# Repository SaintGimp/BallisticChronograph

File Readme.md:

This project is heavily based on https://github.com/td0g/ballistic_chronograph_mk2 but modified to use phototransistors rather than photodiodes, mostly because components for the boost converter in the original design are really hard to source right now, and I also wanted to optimize for my own use cases.

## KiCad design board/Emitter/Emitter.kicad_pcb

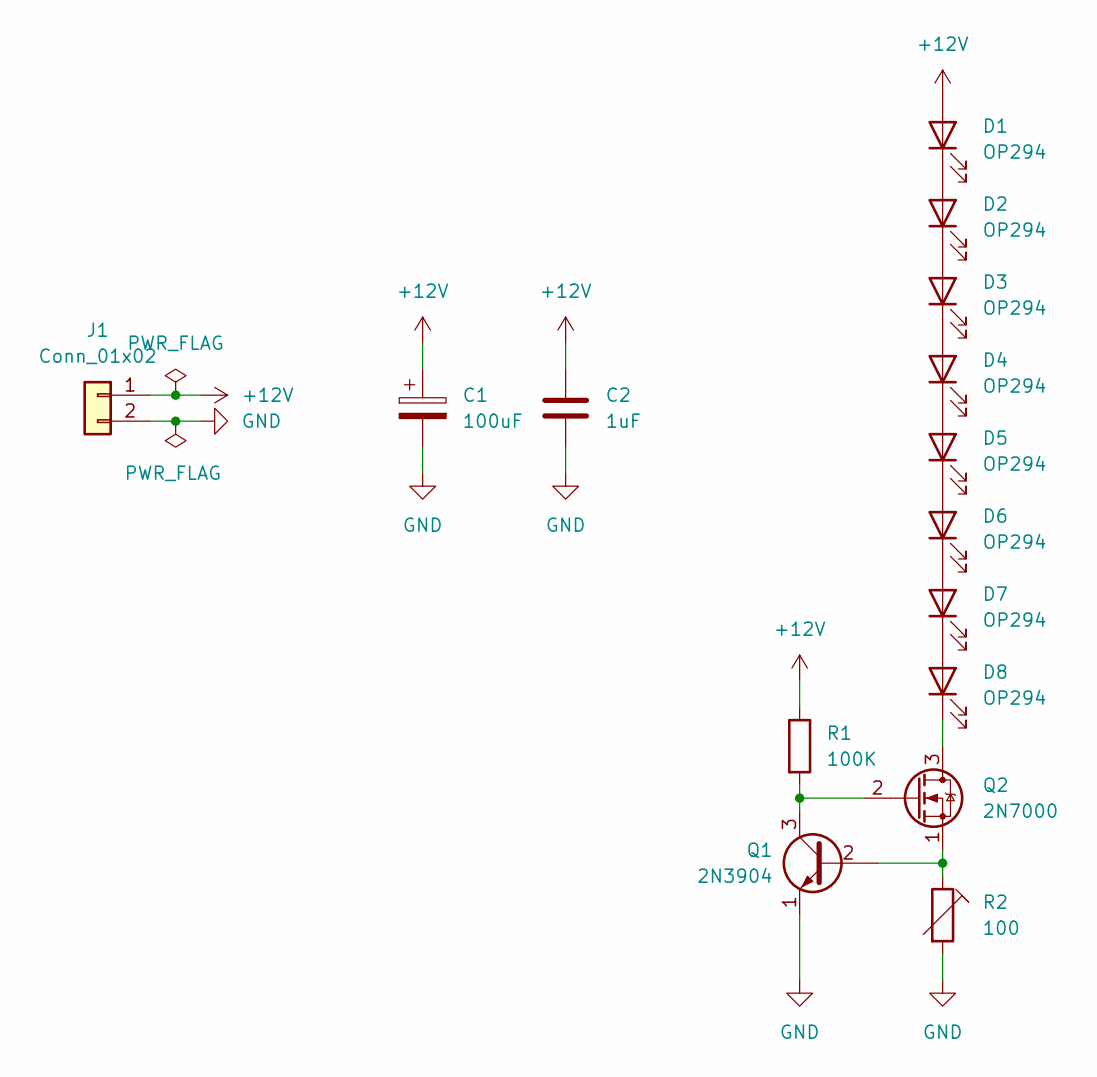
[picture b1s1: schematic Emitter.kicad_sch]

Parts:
C1: 100uF; CP_Radial_D6.3mm_P2.50mm
C2: 1uF; C_Disc_D4.7mm_W2.5mm_P5.00mm
D1, D2, D3, D4, D5, D6, D7, D8: OP294; LED_D5.0mm_IRGrey
J1: Conn_01x02; TerminalBlock_TE_282834-2_1x02_P2.54mm_Horizontal
Q1: 2N3904; TO-92_Inline
Q2: 2N7000; TO-92_Inline
R1: 100K; R_Axial_DIN0207_L6.3mm_D2.5mm_P7.62mm_Horizontal
R2: 100; Potentiometer_Bourns_3296W_Vertical

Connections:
+12V: C1.1, C2.1, D1.2 (A), J1.1, R1.1
GND: C1.2, C2.2, J1.2, Q1.1 (E), R2.2
unnamed: D1.1 (K), D2.2 (A)
unnamed: D2.1 (K), D3.2 (A)
unnamed: D3.1 (K), D4.2 (A)
unnamed: D4.1 (K), D5.2 (A)
unnamed: D5.1 (K), D6.2 (A)
unnamed: D6.1 (K), D7.2 (A)
unnamed: D7.1 (K), D8.2 (A)
unnamed: D8.1 (K), Q2.3 (D)
unnamed: Q1.2 (B), Q2.1 (S), R2.1
unnamed: Q1.3 (C), Q2.2 (G), R1.2

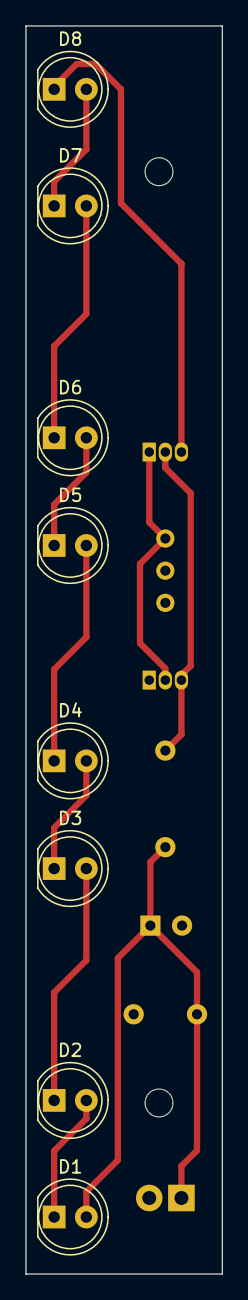
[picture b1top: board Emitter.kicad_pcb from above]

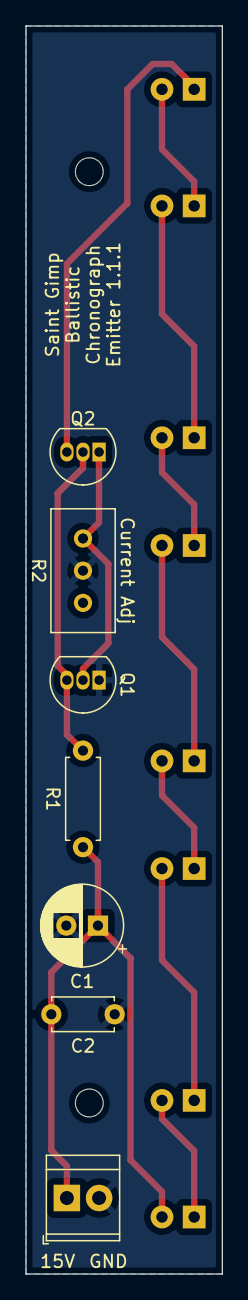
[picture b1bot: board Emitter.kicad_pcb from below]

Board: 2 copper layers, 15.5 x 98.5 mm, 15 parts (7 on the bottom side), 12 nets.

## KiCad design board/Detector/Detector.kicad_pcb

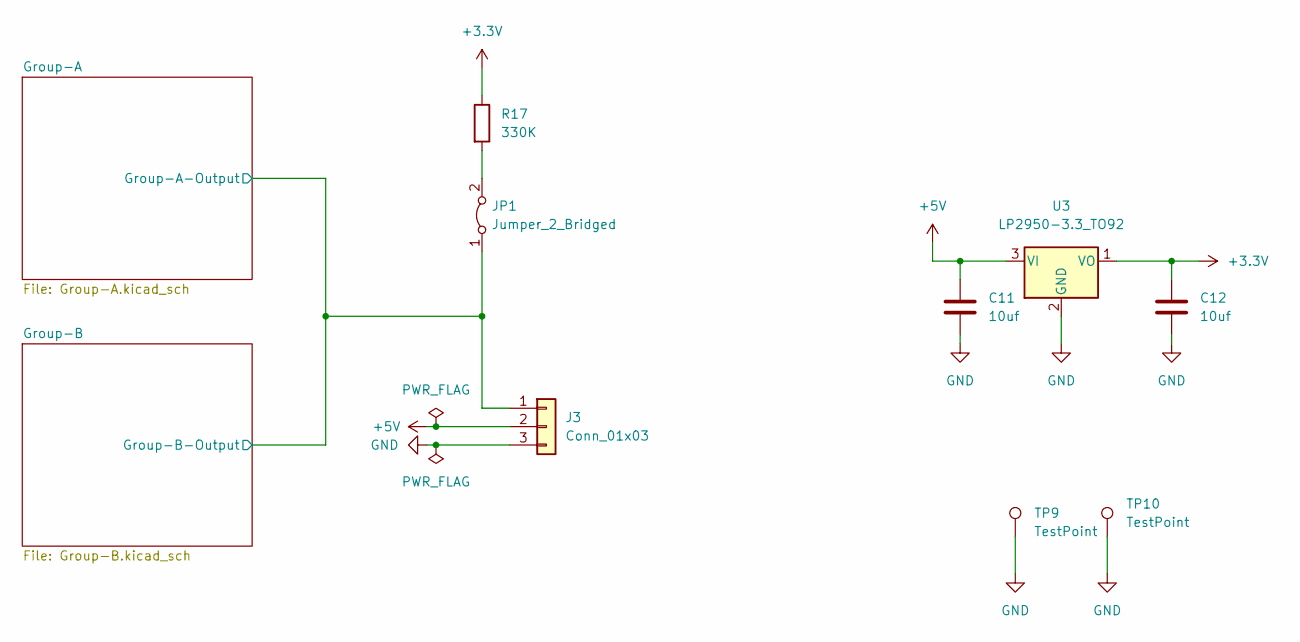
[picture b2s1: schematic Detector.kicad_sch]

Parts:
C11, C12: 10uf; C_1206_3216Metric_Pad1.33x1.80mm_HandSolder
J3: Conn_01x03; TerminalBlock_TE_282834-3_1x03_P2.54mm_Horizontal
JP1: Jumper_2_Bridged; SolderJumper-2_P1.3mm_Bridged_Pad1.0x1.5mm
R17: 330K; R_0805_2012Metric_Pad1.20x1.40mm_HandSolder
TP9, TP10: TestPoint; PinHeader_1x01_P2.54mm_Vertical
U3: LP2950-3.3_TO92; TO-92_Inline

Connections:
+3V3: C12.1, R17.1, U3.1 (VO); also elsewhere on the board
+5V: C11.1, J3.2, U3.3 (VI)
/Group-A/Group-A-Output: J3.1, JP1.1 (A); also elsewhere on the board
GND: C11.2, C12.2, J3.3, TP9.1, TP10.1, U3.2 (GND); also elsewhere on the board
unnamed: JP1.2 (B), R17.2

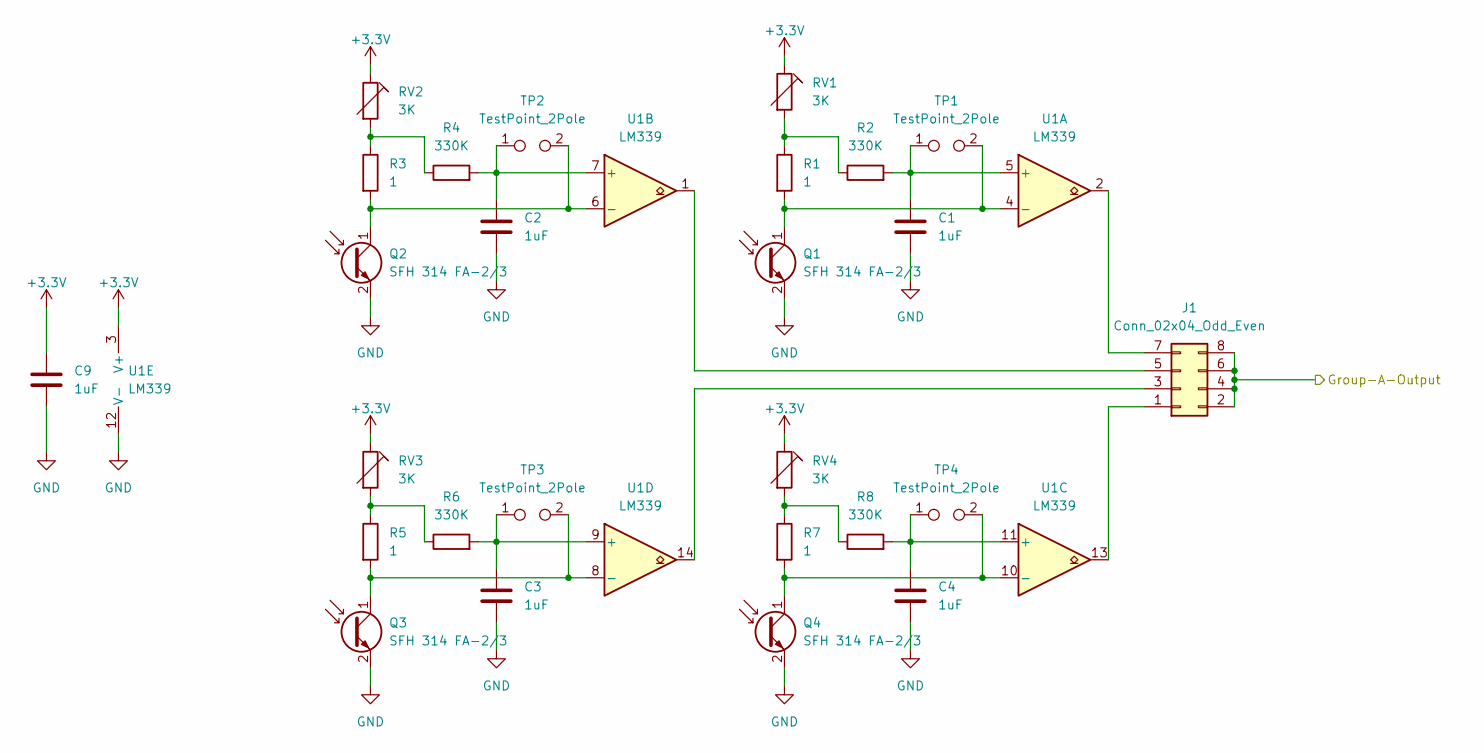
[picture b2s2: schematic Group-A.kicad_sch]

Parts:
C1, C2, C3, C4, C9: 1uF; C_0805_2012Metric_Pad1.18x1.45mm_HandSolder
J1: Conn_02x04_Odd_Even; PinHeader_2x04_P2.54mm_Vertical
Q1, Q2, Q3, Q4: SFH 314 FA-2/3; LED_D3.0mm_IRBlack
R1, R3, R5, R7: 1; R_0805_2012Metric_Pad1.20x1.40mm_HandSolder
R2, R4, R6, R8: 330K; R_0805_2012Metric_Pad1.20x1.40mm_HandSolder
RV1, RV2, RV3, RV4: 3K; 3362P_1
TP1, TP2, TP3, TP4: TestPoint_2Pole; PinHeader_1x02_P2.54mm_Vertical
U1: LM339; TSSOP-14_4.4x5mm_P0.65mm

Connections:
+3V3: C9.1, RV1.1, RV2.1, RV3.1, RV4.1, U1.3 (V+); also elsewhere on the board
/Group-A/Group-A-Output: J1.2, J1.4, J1.6, J1.8; also elsewhere on the board
GND: C1.2, C2.2, C3.2, C4.2, C9.2, Q1.2 (E), Q2.2 (E), Q3.2 (E), Q4.2 (E), U1.12 (V-); also elsewhere on the board
unnamed: C1.1, R2.2, TP1.1, U1.5 (+)
unnamed: C2.1, R4.2, TP2.1, U1.7 (+)
unnamed: C3.1, R6.2, TP3.1, U1.9 (+)
unnamed: C4.1, R8.2, TP4.1, U1.11 (+)
unnamed: J1.1, U1.13
unnamed: J1.3, U1.14
unnamed: J1.5, U1.1
unnamed: J1.7, U1.2
unnamed: Q1.1 (C), R1.2, TP1.2, U1.4 (-)
unnamed: Q2.1 (C), R3.2, TP2.2, U1.6 (-)
unnamed: Q3.1 (C), R5.2, TP3.2, U1.8 (-)
unnamed: Q4.1 (C), R7.2, TP4.2, U1.10 (-)
unnamed: R1.1, R2.1, RV1.2
unnamed: R3.1, R4.1, RV2.2
unnamed: R5.1, R6.1, RV3.2
unnamed: R7.1, R8.1, RV4.2

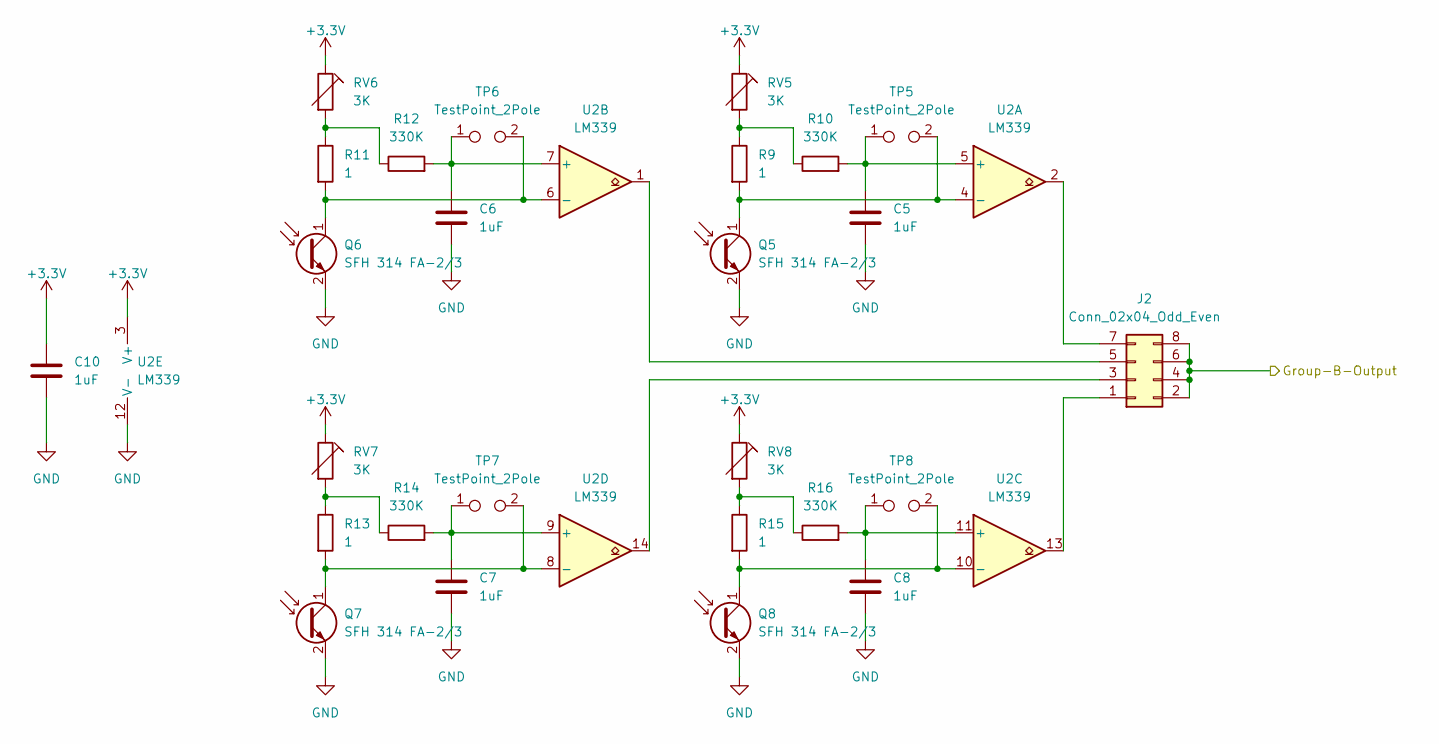
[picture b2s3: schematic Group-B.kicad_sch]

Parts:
C5, C6, C7, C8, C10: 1uF; C_0805_2012Metric_Pad1.18x1.45mm_HandSolder
J2: Conn_02x04_Odd_Even; PinHeader_2x04_P2.54mm_Vertical
Q5, Q6, Q7, Q8: SFH 314 FA-2/3; LED_D3.0mm_IRBlack
R9, R11, R13, R15: 1; R_0805_2012Metric_Pad1.20x1.40mm_HandSolder
R10, R12, R14, R16: 330K; R_0805_2012Metric_Pad1.20x1.40mm_HandSolder
RV5, RV6, RV7, RV8: 3K; 3362P_1
TP5, TP6, TP7, TP8: TestPoint_2Pole; PinHeader_1x02_P2.54mm_Vertical
U2: LM339; TSSOP-14_4.4x5mm_P0.65mm

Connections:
+3V3: C10.1, RV5.1, RV6.1, RV7.1, RV8.1, U2.3 (V+); also elsewhere on the board
/Group-A/Group-A-Output: J2.2, J2.4, J2.6, J2.8; also elsewhere on the board
GND: C5.2, C6.2, C7.2, C8.2, C10.2, Q5.2 (E), Q6.2 (E), Q7.2 (E), Q8.2 (E), U2.12 (V-); also elsewhere on the board
unnamed: C5.1, R10.2, TP5.1, U2.5 (+)
unnamed: C6.1, R12.2, TP6.1, U2.7 (+)
unnamed: C7.1, R14.2, TP7.1, U2.9 (+)
unnamed: C8.1, R16.2, TP8.1, U2.11 (+)
unnamed: J2.1, U2.13
unnamed: J2.3, U2.14
unnamed: J2.5, U2.1
unnamed: J2.7, U2.2
unnamed: Q5.1 (C), R9.2, TP5.2, U2.4 (-)
unnamed: Q6.1 (C), R11.2, TP6.2, U2.6 (-)
unnamed: Q7.1 (C), R13.2, TP7.2, U2.8 (-)
unnamed: Q8.1 (C), R15.2, TP8.2, U2.10 (-)
unnamed: R9.1, R10.1, RV5.2
unnamed: R11.1, R12.1, RV6.2
unnamed: R13.1, R14.1, RV7.2
unnamed: R15.1, R16.1, RV8.2

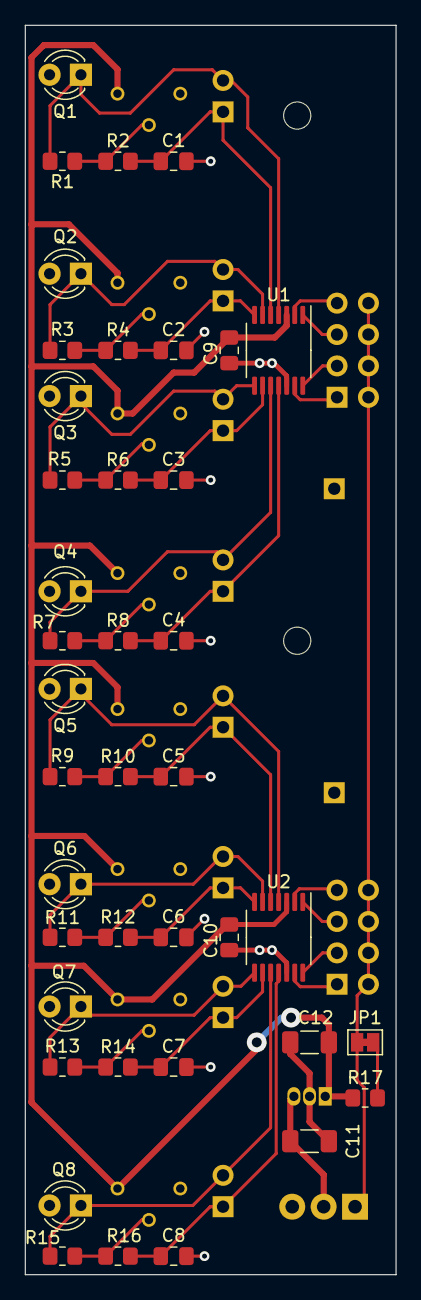
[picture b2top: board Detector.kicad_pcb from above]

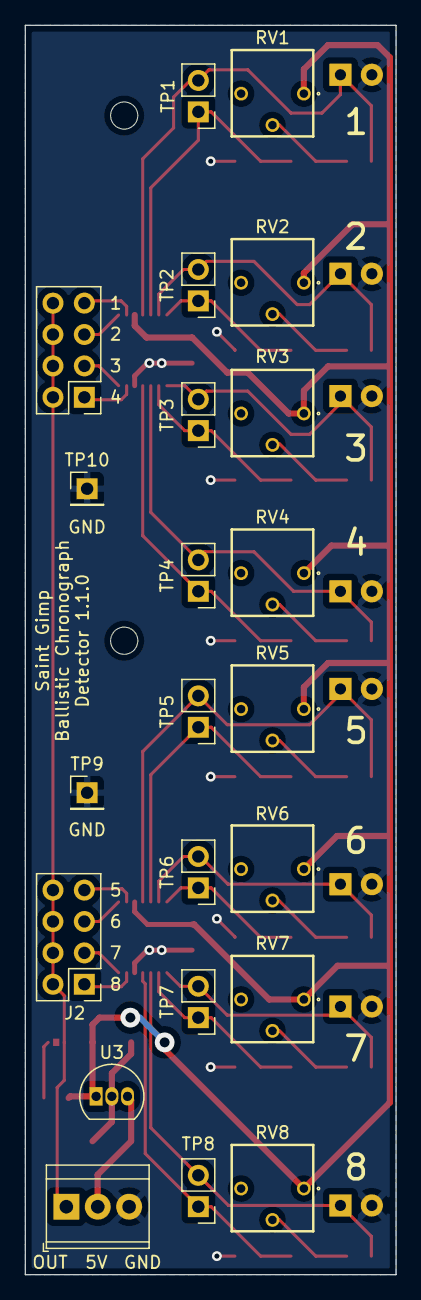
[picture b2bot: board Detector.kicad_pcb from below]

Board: 2 copper layers, 30.0 x 101.1 mm, 62 parts (22 on the bottom side), 37 nets.

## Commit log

2021-11-24 Detector board checkpoint
2021-11-25 Complete layout with top pour
2021-11-26 Final version of detector and gerbers
2021-11-26 First rev of emitter
2021-11-26 Emitter gerbers
2021-12-10 Fix the order of jumper links
2021-12-10 Add license and readme
2021-12-10 Increase led and phototransistor spacing to better handle angled holes
2021-12-10 Adjust values
2021-12-10 Detector changes to better control overall bias level
2021-12-14 Changed connectors, 3D models, added test points
2021-12-14 Updated gerbers
2021-12-23 Update silkscreen on emitter
2021-12-25 Initial prototype code using Featherwing OLED
2022-06-14 Reduce sensitivity so we don't trigger on dust
2022-08-06 Count unfinished events
